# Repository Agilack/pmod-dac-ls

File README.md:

PMOD Low speed DAC
==================

This project is digitally controlled voltage source into a PMOD form factor.
An digital-to-analog converter coupled with an amplifier stage offer a
variable voltage on the output (hundred on mili-amps available).

License
-------

This project is OpenHardware. You can reuse all files and materials under terms
of the Creative Commons Share Alike license.

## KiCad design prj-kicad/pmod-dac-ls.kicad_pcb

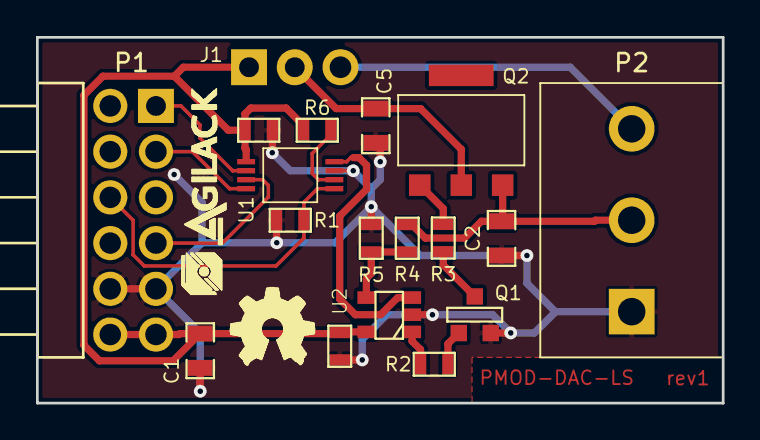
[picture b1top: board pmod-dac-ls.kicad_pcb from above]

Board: 2 copper layers, 38.1 x 20.3 mm, 20 parts (0 on the bottom side), 16 nets.

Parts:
C1, C2, C5: 10uF; SMD0805
C3, C4: 100nF; SMD0603
J1: JUMPER; CONN_3
LOGO-OHW: VAL**; logo-ohw
P1: PMOD; CONN_PMOD-Male
P2: CONN_3; CONN_MC000035
Q1: BC846; SOT23-3
Q2: BCP52T; SOT223
R1, R4: 10k; SMD0603
R2, R3: 1k; SMD0603
R5: R; SMD0603
R6: 0; SMD0603
U1: MCP4921; MSOP-8
U2: MCP6001; SOT23-5
agilack-11.5: 450px; logo-agilack-11.5

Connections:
+3.3V: C1.1, C3.1, C4.1, J1.1, P1.6, P1.12, R6.1, U1.1, U2.5
+VExt: J1.3, P2.3
GND: C1.2, C2.2, C3.2, C4.2, C5.2, P1.5, P1.11, P2.1, Q1.2, R1.2, R5.1, U1.7, U2.2
unnamed: C2.1, P2.2, Q2.3, R4.1
unnamed: C5.1, J1.2, Q2.2
unnamed: Q1.1, R2.1
unnamed: Q1.3, R3.2
unnamed: Q2.1, R3.1
unnamed: R2.2, U2.1
unnamed: R4.2, R5.2, U2.4
unnamed: R6.2, U1.6
unnamed: U1.8, U2.3
PMOD_CS: P1.1, U1.2
PMOD_GPIO: P1.9, R1.1, U1.5
PMOD_MOSI: P1.2, U1.4
PMOD_SCK: P1.4, U1.3

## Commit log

2020-03-27 = Create initial design (schematics + routing)
2020-03-31 = ADD: Create production files for rev1

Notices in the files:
prj-kicad/pmod-dac-ls.kicad_pcb:
License: CC-by-SA
